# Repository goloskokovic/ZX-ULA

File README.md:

ULA CPLD Project - Clone of the ZX Spectrum ULA.

This project aims to replace a custom-made component for the 8-bit microcomputer ZX Spectrum manufactured by the English company Sinclair Research.

Details

All this work was based on the work of Chris Smith [1] and done jointly by the project authors. Thanks to the people from the Brazilian discussion lists "ClubedoTK" [2] and "TK90X" [3] who encouraged and helped in the development of this project.

On the website [4] there is a small diary created by Victor Trucco describing the steps during the development of the project.

The project [5] has two revisions, rev1 and rev2, each in a separate folder. In each revision there is a folder with the PCB design, a folder with the Gerber fabrication files and a folder with the CPLD source code project. The software version used for PCB design was Cadsoft Eagle, and the software used for CPLD design was Altera Quartus version 10.1sp1.

In the "VHDL Version" folder, there is a version of the CPLD code written entirely in VHDL, for both Altera and Xilinx CPLDs. This code was not used in the final ULA CPLD. This is the version used here.

The final product is a small board designed to be inserted directly into the socket of the original integrated circuit, thus replacing the defective component, with the advantage of having a 15kHz analog RGB output for direct use with compatible monitors.

Assembly

Solder the SMD components, obtain an 80-pin turned terminal block, cut it in half for the two 40-pin sides. The CPLD occupies the space of four pins on each side of the turned terminal block, so it is necessary to cut the 4 central pins of each block to make an SMD solder joint at these points.

Place the block in position to find out which pins should be cut, cut with thin cutting pliers to leave it flush with the PCB. Use a 40-pin turned socket and plug the blocks into the socket for aligned soldering. Place the PCB on top of the block and fit the uncut pins into their respective holes and solder them. To solder the 8 cut pins (4 on each side), place the soldering iron tip on one side to heat the PCB and the pin header simultaneously, and apply the solder from the other side. Check with a magnifying glass to ensure successful soldering.

If using the 15kHz RGB output, solder a 90-degree pin header to the PCB, and in revision 2, solder the synchronization jumper. You can choose which type of synchronization will go to the monitor, separate or composite. Depending on the monitor, one type may be better than the other, so it may be necessary to test both types; however, the separate synchronization option has greater compatibility with monitors.

In the Photos folder, there are some photos of the first prototype built.

CPLD Programming

To program the CPLD, a USB Blaster device specific to Altera CPLDs is required. In PCB rev1, the contact points for the programming signals are spread across the PCB, requiring the construction of a "nail bed" or soldering of wires to the points. For rev2, the signals are arranged in a 1x6 connector. The signal names are on the PCB silkscreen. It is necessary to use an external 5V power supply and apply 5V to the VCC pin of the USB Blaster, as it does not power the device but detects if it is powered.

Open the project in Quartus software and go to the programmer. Power the PCB and the USB Blaster and click "Program". If there is a failure in this step, check the connections and check if 5V is going to the USB Blaster. The file needed for programming is called "ULA.pof".

Usage

It is highly recommended to replace the ULA socket on the ZX Spectrum PCB with a machined socket, however, it is possible to use the original. Carefully plug the ULA PCB into the TK socket, pressing slowly to avoid bending any pins. If everything goes well, just turn on the computer and enjoy your new ULA.

Links

[1] http://www.zxdesign.info/thebeginning.shtml [2] http://br.groups.yahoo.com/group/ClubedoTK/ [3] http://br.groups.yahoo.com/group/TK90X/ [4] http://www.victortrucco.com/TK/ULATKCPLD/ULATKCPLD.asp [5] https://github.com/fbelavenuto/tk90x_ula

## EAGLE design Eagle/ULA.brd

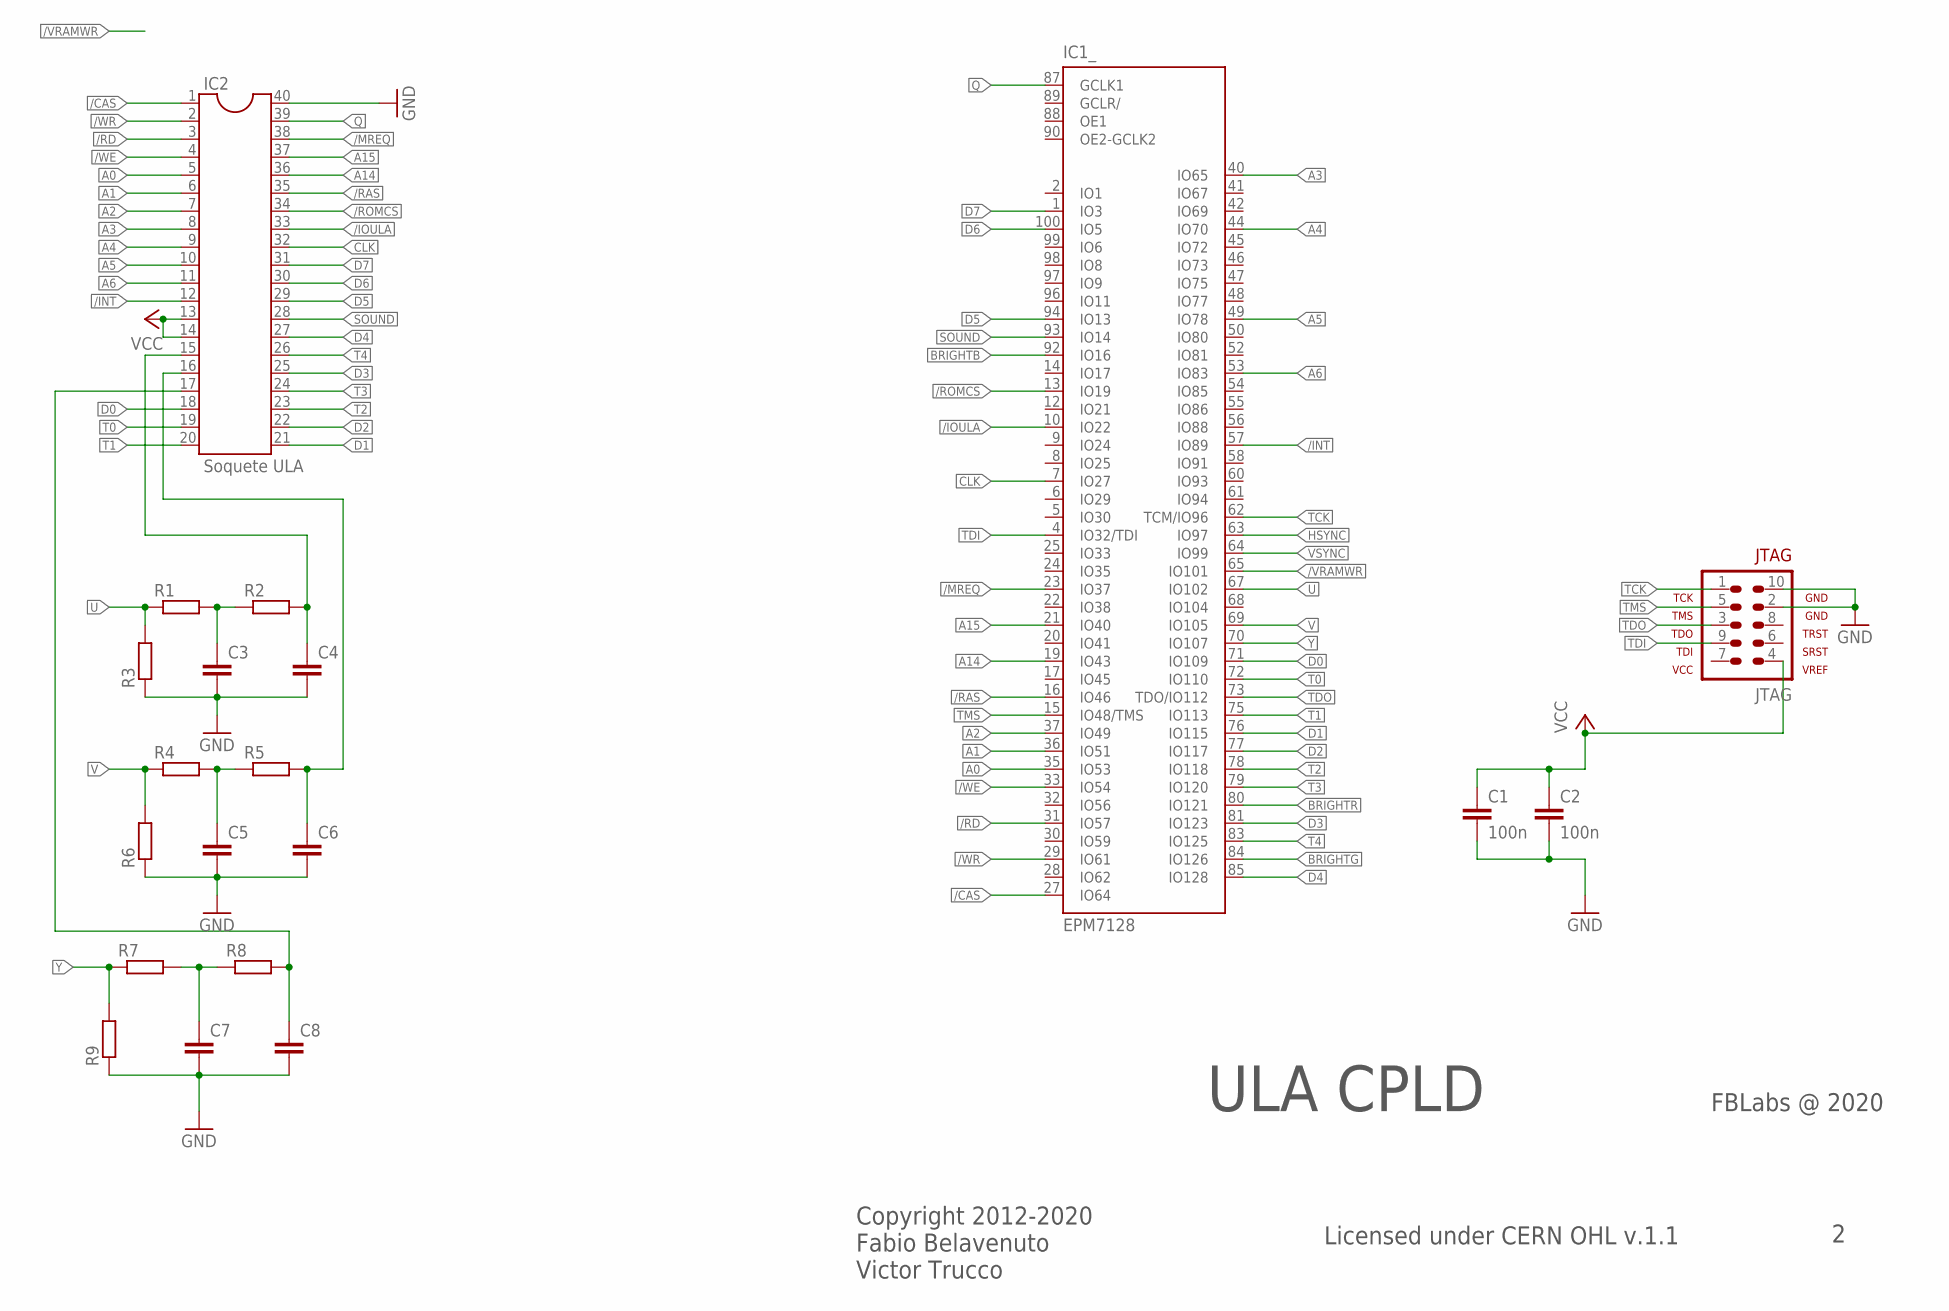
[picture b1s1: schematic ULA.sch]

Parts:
C1, C2: 100n; C1206
C3, C4, C5, C6, C7, C8: C-EUC0805K; C0805K
IC1: EPM7128; TQFP100
IC2: Soquete ULA; DIL40
JTAG: AVR-JTAG-10
R1, R2, R3, R4, R5, R6, R7, R8, R9: R-EU_M0805; M0805

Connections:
/CAS: IC1.27 (IO64), IC2.1
/INT: IC1.57 (IO89), IC2.12
/IOULA: IC1.10 (IO22), IC2.33
/MREQ: IC1.23 (IO37), IC2.38
/RAS: IC1.16 (IO46), IC2.35
/RD: IC1.31 (IO57), IC2.3
/ROMCS: IC1.13 (IO19), IC2.34
/VRAMWR: IC1.65 (IO101)
/WE: IC1.33 (IO54), IC2.4
/WR: IC1.29 (IO61), IC2.2
A0: IC1.35 (IO53), IC2.5
A1: IC1.36 (IO51), IC2.6
A2: IC1.37 (IO49), IC2.7
A3: IC1.40 (IO65), IC2.8
A4: IC1.44 (IO70), IC2.9
A5: IC1.49 (IO78), IC2.10
A6: IC1.53 (IO83), IC2.11
A14: IC1.19 (IO43), IC2.36
A15: IC1.21 (IO40), IC2.37
BRIGHTB: IC1.92 (IO16)
BRIGHTG: IC1.84 (IO126)
BRIGHTR: IC1.80 (IO121)
CLK: IC1.7 (IO27), IC2.32
D0: IC1.71 (IO109), IC2.18
D1: IC1.76 (IO115), IC2.21
D2: IC1.77 (IO117), IC2.22
D3: IC1.81 (IO123), IC2.25
D4: IC1.85 (IO128), IC2.27
D5: IC1.94 (IO13), IC2.29
D6: IC1.100 (IO5), IC2.30
D7: IC1.1 (IO3), IC2.31
GND: C1.2, C2.2, C3.2, C4.2, C5.2, C6.2, C7.2, C8.2, IC1.11 (GND), IC1.26 (GND), IC1.38 (GND), IC1.43 (GND), IC1.59 (GND), IC1.74 (GND), IC1.86 (GND), IC1.95 (GND), IC2.40, JTAG.2, JTAG.10, R3.1, R6.1, R9.1
HSYNC: IC1.63 (IO97)
unnamed: C5.1, R4.2, R5.1
unnamed: C3.1, R1.2, R2.1
unnamed: C4.1, IC2.15, R2.2
unnamed: C6.1, IC2.16, R5.2
unnamed: C7.1, R7.2, R8.1
unnamed: C8.1, IC2.17, R8.2
Q: IC1.87 (GCLK1), IC2.39
SOUND: IC1.93 (IO14), IC2.28
T0: IC1.72 (IO110), IC2.19
T1: IC1.75 (IO113), IC2.20
T2: IC1.78 (IO118), IC2.23
T3: IC1.79 (IO120), IC2.24
T4: IC1.83 (IO125), IC2.26
TCK: IC1.62 (TCM/IO96), JTAG.1
TDI: IC1.4 (IO32/TDI), JTAG.9
TDO: IC1.73 (TDO/IO112), JTAG.3
TMS: IC1.15 (IO48/TMS), JTAG.5
U: IC1.67 (IO102), R1.1, R3.2
V: IC1.69 (IO105), R4.1, R6.2
VCC: C1.1, C2.1, IC1.39 (VCC), IC1.91 (VCC), IC2.13, IC2.14, JTAG.4
VCCIO: IC1.3 (VCCIO), IC1.18 (VCCIO), IC1.34 (VCCIO), IC1.51 (VCCIO), IC1.66 (VCCIO), IC1.82 (VCCIO)
VSYNC: IC1.64 (IO99)
Y: IC1.70 (IO107), R7.1, R9.2

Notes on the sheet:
ULA CPLD
Licensed under CERN OHL v.1.1
Copyright 2012-2020 Fabio Belavenuto Victor Trucco
FBLabs @ 2020

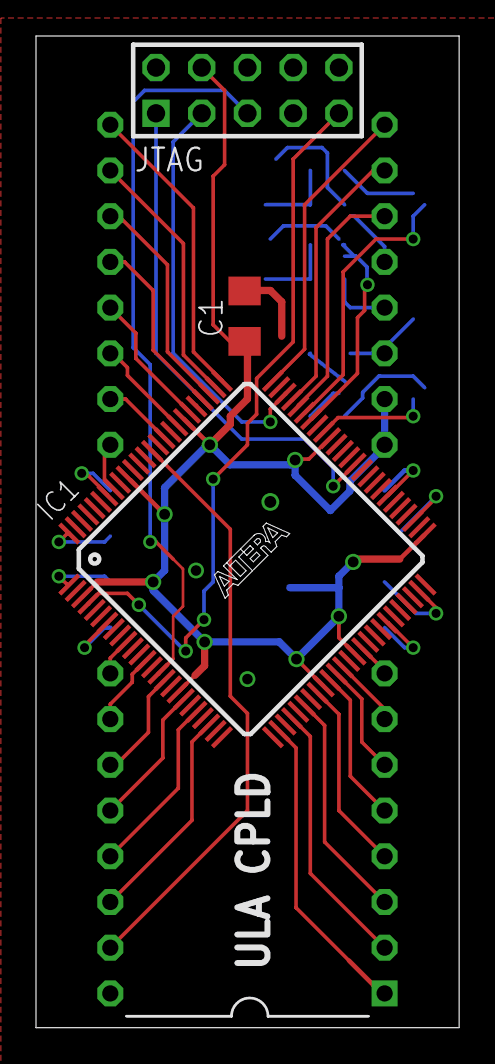
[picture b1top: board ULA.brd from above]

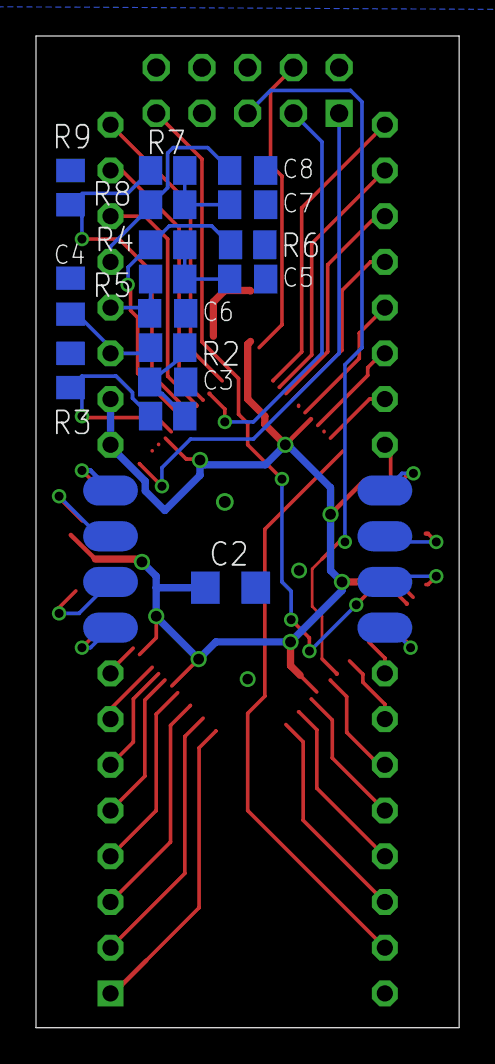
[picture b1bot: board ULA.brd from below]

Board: 2 copper layers, 23.5 x 55.1 mm, 20 parts (16 on the bottom side), 50 nets.

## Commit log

2024-09-06 v0.1
2024-09-06 ZX ULA internal clocks and YUV dac
2024-09-08 updated YUV equations
2024-09-09 added filters for PWM
2024-09-09 PWM DAC
    https://github.com/rcmschiavi/PWM-in-VHDL/blob/master/PWM.vhd
2024-09-09 CPLD pinout update
2024-09-27 YUV PWM
2024-09-27 formatting
2024-09-30 free macrocells
2024-11-21 YUV optimization
2025-07-10 VC -> vc
2025-11-04 Initialize README with project details and instructions
    Added detailed project description, assembly instructions, CPLD programming guide, and usage recommendations.
2026-05-19 Claude Haiku fix
2026-05-20 Raptor mini fix
